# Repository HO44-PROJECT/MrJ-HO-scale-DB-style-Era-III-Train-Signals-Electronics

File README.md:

# Railway HO project Signals and electronics for my HO scale railway project

This is my own project for building model railway HO scale (1:87) Deutsche Bundesbahn (DB) style Era III (1945-1970) Train Signals following this specification.

This is part of a complete project involving:

- 3D printing: the signal bodies, 3 faces ([Maker World](https://makerworld.com/en/models/682526-mrj-ho-scale-db-signals-era-iii-3x-faces))
- Electronics (PCB design and soldering) ([github](https://github.com/HO44-PROJECT/MrJ-HO-scale-DB-style-Era-III-Train-Signals-Electronics))
- Arduino code (demo, DCC and JMRI integration) ([github](https://github.com/HO44-PROJECT/MrJ-HO-scale-DB-style-Era-III-Train-Signals-Arduino-Demo-Code))

## Another project to drive the signals

[MrJ-LayoutFX](https://github.com/HO44-PROJECT/MrJ-LayoutFX) grew out of these signals. It gives you a control
interface for an ESP32 that is driven by DCC commands and can generate lighting effects (signals, beacons, traffic
lights, campfires...) and drive other peripherals. You can flash it straight from your browser.
It is designed to work with a custom PCB with built-in DCC decoding,
[MrJ-LayoutFX-ESP32-PCB](https://github.com/HO44-PROJECT/MrJ-LayoutFX-ESP32-PCB) (ESP32 DevKitC), and also exists for
the Arduino Nano with [MrJ-LayoutFX-Nano-PCB](https://github.com/HO44-PROJECT/MrJ-LayoutFX-Nano-PCB).

This is what you will be able to build:

# What this repository provides

- the **gerber files** of the 2 PCB versions (production and breadboard), ready to send to a manufacturer
- the **wiring and test elements**: the level (VCC / GND) to apply on each wire for every signal aspect and every wiring test, and Fritzing parts to draw your circuit

**[Try the interactive 3D viewer](https://ho44-project.github.io/MrJ-HO-scale-DB-style-Era-III-Train-Signals-Electronics/documentation/prod/MrJ-DB-Era3-prod-viewer.html)**
(production PCB; the [breadboard version](https://ho44-project.github.io/MrJ-HO-scale-DB-style-Era-III-Train-Signals-Electronics/documentation/breadboard/MrJ-DB-Era3-breadboard-viewer.html) is there too).
Pick a signal, then an aspect: all LEDs off, all on, Hp0, Hp1...
The 3D view also helps you **place the LEDs**: turn the board around and see which LED goes where, and which ones
light for each aspect.

The breadboard version, for the three signals (block, entry, exit):

| Block signal | Entry signal | Exit signal |
|---|---|---|
|  |  |  |

## Production or breadboard?

Both boards have the same circuit and the same LEDs. They differ by how you connect them:

- **Production PCB**: the board that goes inside the signal. You solder your wires directly to the pads.
  This is the one to order for your layout.
- **Breadboard PCB**: the same board with pin headers, and room to solder the resistors on it.
  Plug it on a breadboard to test the wiring, the resistors and your controller (Arduino, DCC, JMRI) *before*
  building the real signals. It is a test tool, not meant to be installed on the layout.

If you only want to build the signals, order the production PCB. Order the breadboard one too if you want to test first.

## More pictures

The [images](images/) directory holds many pictures of the assembly (soldering with helpers, testing a signal,
disassembly), of the design (board, details, parts) and of the finished block, entry and exit signals.
The assembly pictures show the **procedure to follow**, in particular how to **use the jig**: a 3D printed part
that holds the LEDs and the PCB in place while you solder them.

# Resources

[wikipedia signals in Germany](https://en.wikipedia.org/wiki/Railway_signals_in_Germany)

These sites were a great source of inspiration:
* [stummi forum (DE)](https://www.stummiforum.de/t174376f21-Viessman-Signalbr-cke-mit-Arduino-gesteuert.html)
* [digital bahn (DE)] (https://www.digital-bahn.de/info_kompo/signale.htm)

# Project

This project contains Kicad project files and gerber to build PCBs using 1.8mm LEDs.

This PCB uses charlieplexing to reduce the number of wires. It is possible to build a block signal, input signal, or output signal with this PCB.
I designed my own wiring path to avoid using the POV effect to light multiple LEDs. Each situation for each signal is a simple combination of HIGH and LOW signals on all 4 pins.

It's possible to reduce the number of wires for the "Block Signal" (only 2 wires required) and the "Entry Signal" (only 3 wires required). See [documentation](documentation/).

I also need a special breadboard version to ease tests. This version allows soldering of resistors.

The **gerber.zip** files are enough to build the PCB from a manufacturer such as [jlcpcb](https://jlcpcb.com/). See the [release](release/) directory.

The PCB is designed to fit inside the 3D printed signals: see the
[3D model on Maker World](https://makerworld.com/en/models/682526-mrj-ho-scale-db-signals-era-iii-3x-faces).

# History

The version 2 is smaller than the version 1.
It solves the "shunting signal" Hp0 + Sh1 did not work because the right white LED did not light up.

This v3 is a better version as it fixes a distributed current problem.

# Repository content

| Directory | Content |
|---|---|
| [release](release/) | Gerber zips, ready to send to a PCB manufacturer (production and breadboard boards). |
| [source](source/) | KiCad 10 projects (schematic and PCB) of the two boards. |
| [library](library/) | KiCad footprints, 3D models and drawings of the 1.8 mm LEDs. |
| [documentation](documentation/) | Renders, interactive 3D viewers, and the wire levels (VCC / GND) for each signal aspect. |
| [images](images/) | Pictures of the assembly, the design and the finished signals. |
| [fritzing](fritzing/) | [Fritzing](https://fritzing.org) parts of the signals, to draw your circuit. |

The 3D printed signals themselves are on [Maker World](https://makerworld.com/en/models/682526-mrj-ho-scale-db-signals-era-iii-3x-faces).

The interactive viewers in [documentation](documentation/) must be served over http (for example from GitHub Pages).

# BOM:
* a PCB per signal. I ordered mine 0.8mm thickness from jlcpcb.com simply by uploading the gerber.zip file.
* 2 to 4 resistors 1/4 W from everywhere: 470 ohm for a 3.3 V supply, 1 kohm for a 5 V supply
* 1.8mm LEDs. I bought mine from aliexpress.com.

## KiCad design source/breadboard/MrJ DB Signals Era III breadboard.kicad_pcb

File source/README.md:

# source

KiCad 10 projects of the signal boards (schematic + PCB). Open the `.kicad_pro` file in KiCad.

| Folder | Board |
|---|---|
| `prod/` | Production PCB, wires are soldered to the pads. |
| `breadboard/` | Same circuit with pin headers, for prototyping on a breadboard. |

Each folder contains the project (`.kicad_pro`), the schematic (`.kicad_sch`) and the PCB (`.kicad_pcb`).
The LED footprints and 3D models come from [`../library`](../library).

These files are the single source of truth: everything in `documentation/`, `fritzing/` and
`release/` is derived from them.

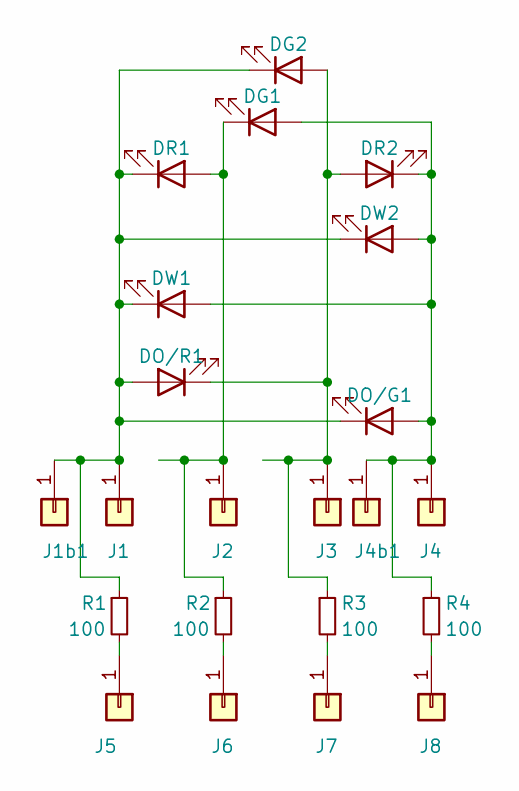
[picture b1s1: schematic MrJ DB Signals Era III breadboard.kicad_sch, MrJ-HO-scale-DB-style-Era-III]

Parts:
DG1, DG2: LED; LED_D1.8mm_W3.3mm_H2.4mm_mine
DO/G1: LED; LED_D1.8mm_W3.3mm_H2.4mm_mine
DO/R1: LED; LED_D1.8mm_W3.3mm_H2.4mm_mine
DR1, DR2: LED; LED_D1.8mm_W3.3mm_H2.4mm_mine
DW1, DW2: LED; LED_D1.8mm_W3.3mm_H2.4mm_mine
J1, J1b1, J2, J3, J4, J4b1: Conn_01x01; SolderWirePad_1x01_SMD_1x2mm
J5, J6, J7, J8: Conn_01x01; Pin_D0.9mm_L10.0mm_W2.4mm_FlatFork
R1, R2, R3, R4: 100; R_Axial_DIN0204_L3.6mm_D1.6mm_P7.62mm_Horizontal

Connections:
unnamed: DG1.2 (A), DO/G1.2 (A), DR2.1 (K), DW1.2 (A), DW2.2 (A), J4.1, J4b1.1, R4.1
unnamed: DG1.1 (K), DR1.2 (A), J2.1, R2.1
unnamed: DG2.2 (A), DO/R1.1 (K), DR2.2 (A), J3.1, R3.1
unnamed: DG2.1 (K), DO/G1.1 (K), DO/R1.2 (A), DR1.1 (K), DW1.1 (K), DW2.1 (K), J1.1, J1b1.1, R1.1
unnamed: J5.1, R1.2
unnamed: J6.1, R2.2
unnamed: J7.1, R3.2
unnamed: J8.1, R4.2

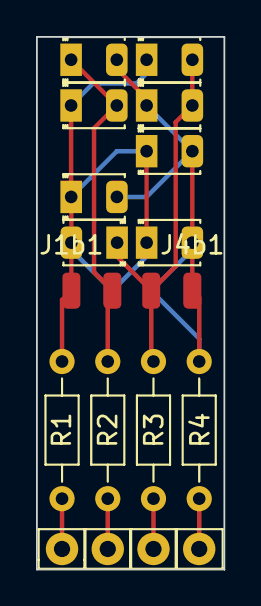
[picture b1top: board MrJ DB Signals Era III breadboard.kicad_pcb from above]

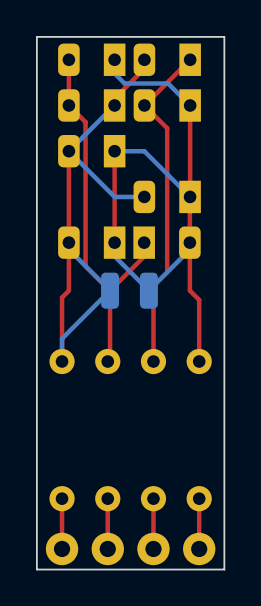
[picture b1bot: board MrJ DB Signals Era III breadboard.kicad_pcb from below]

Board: 2 copper layers, 10.4 x 29.6 mm, 22 parts (2 on the bottom side), 8 nets.

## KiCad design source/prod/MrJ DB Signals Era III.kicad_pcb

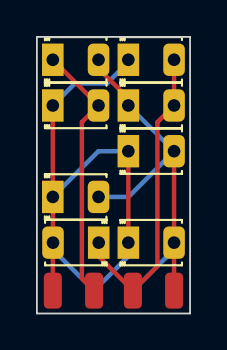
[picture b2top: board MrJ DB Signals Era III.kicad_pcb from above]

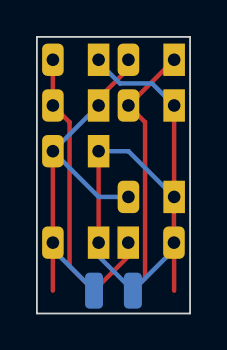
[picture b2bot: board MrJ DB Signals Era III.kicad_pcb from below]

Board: 2 copper layers, 8.5 x 15.4 mm, 14 parts (2 on the bottom side), 4 nets.

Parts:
DG1, DG2: LED; LED_D1.8mm_W3.3mm_H2.4mm_mine
DO/G1: LED; LED_D1.8mm_W3.3mm_H2.4mm_mine
DO/R2: LED; LED_D1.8mm_W3.3mm_H2.4mm_mine
DR1, DR2: LED; LED_D1.8mm_W3.3mm_H2.4mm_mine
DW1, DW2: LED; LED_D1.8mm_W3.3mm_H2.4mm_mine
J1, J1b1, J2, J3, J4, J4b1: Conn_01x01; SolderWirePad_1x01_SMD_1x2mm

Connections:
unnamed: DG1.2 (A), DO/G1.2 (A), DR2.1 (K), DW1.2 (A), DW2.2 (A), J4.1, J4b1.1
unnamed: DG1.1 (K), DR1.2 (A), J2.1
unnamed: DG2.2 (A), DO/R2.1 (K), DR2.2 (A), J3.1
unnamed: DG2.1 (K), DO/G1.1 (K), DO/R2.2 (A), DR1.1 (K), DW1.1 (K), DW2.1 (K), J1.1, J1b1.1

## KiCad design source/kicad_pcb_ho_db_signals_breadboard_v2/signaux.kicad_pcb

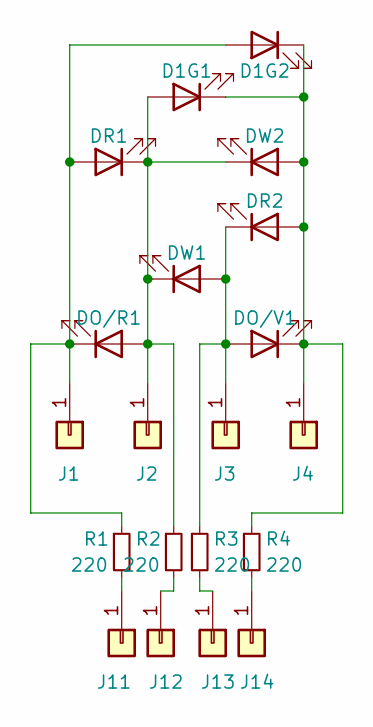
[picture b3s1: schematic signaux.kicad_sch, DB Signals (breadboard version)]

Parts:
D1G1, D1G2: LED; LED_D1.8mm_W3.3mm_H2.4mm_mine
DO/R1: LED; LED_D1.8mm_W3.3mm_H2.4mm_mine
DO/V1: LED; LED_D1.8mm_W3.3mm_H2.4mm_mine
DR1, DR2: LED; LED_D1.8mm_W3.3mm_H2.4mm_mine
DW1, DW2: LED; LED_D1.8mm_W3.3mm_H2.4mm_mine
J1, J2, J3, J4: Conn_01x01; SolderWirePad_1x01_SMD_1x2mm
J11, J12, J13, J14: Conn_01x01; Pin_D0.9mm_L10.0mm_W2.4mm_FlatFork
R1, R2, R3, R4: 220; R_Axial_DIN0204_L3.6mm_D1.6mm_P7.62mm_Horizontal

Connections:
unnamed: D1G1.2 (A), DO/R1.2 (A), DR1.1 (K), DW1.1 (K), DW2.1 (K), J2.1, R2.1
unnamed: D1G1.1 (K), D1G2.1 (K), DO/V1.1 (K), DR2.2 (A), DW2.2 (A), J4.1, R4.1
unnamed: D1G2.2 (A), DO/R1.1 (K), DR1.2 (A), J1.1, R1.1
unnamed: DO/V1.2 (A), DR2.1 (K), DW1.2 (A), J3.1, R3.1
unnamed: J11.1, R1.2
unnamed: J12.1, R2.2
unnamed: J13.1, R3.2
unnamed: J14.1, R4.2

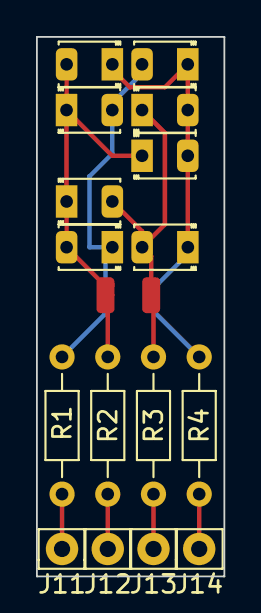
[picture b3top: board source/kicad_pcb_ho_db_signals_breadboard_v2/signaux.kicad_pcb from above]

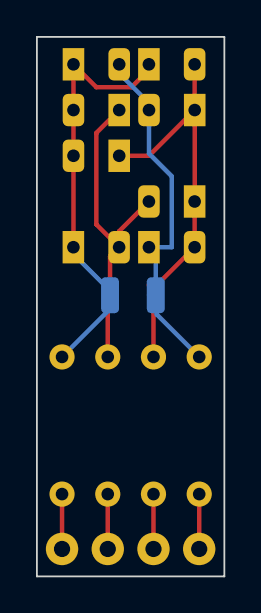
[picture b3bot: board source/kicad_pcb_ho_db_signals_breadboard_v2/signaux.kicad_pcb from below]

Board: 2 copper layers, 10.4 x 30.0 mm, 20 parts (2 on the bottom side), 8 nets.

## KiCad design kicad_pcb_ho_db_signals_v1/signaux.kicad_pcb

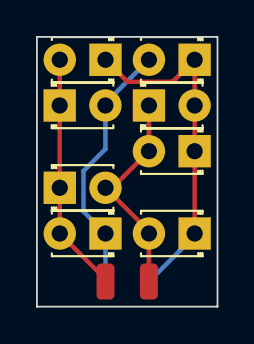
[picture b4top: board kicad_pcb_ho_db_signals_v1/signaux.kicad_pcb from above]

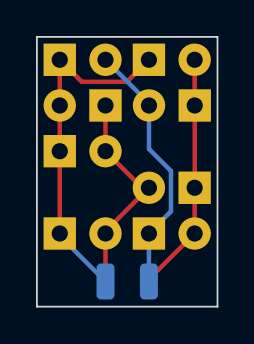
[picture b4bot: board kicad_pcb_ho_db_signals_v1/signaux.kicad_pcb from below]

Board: 2 copper layers, 10.0 x 15.0 mm, 12 parts (2 on the bottom side), 4 nets.

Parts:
D1G1, D1G2, D2R1, D3R1, D4W1, D5W1, D6O1, D7O2: LED; LED_D1.8mm_W3.3mm_H2.4mm
J1, J2, J3, J4: Conn_01x01; SolderWirePad_1x01_SMD_1x2mm

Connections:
unnamed: D1G1.2 (A), D2R1.1 (K), D5W1.1 (K), D6O1.2 (A), J2.1
unnamed: D1G1.1 (K), D1G2.1 (K), D3R1.2 (A), D4W1.1 (K), D7O2.1 (K), J4.1
unnamed: D1G2.2 (A), D2R1.2 (A), D6O1.1 (K), J1.1
unnamed: D3R1.1 (K), D4W1.2 (A), D5W1.2 (A), D7O2.2 (A), J3.1

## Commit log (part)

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2024-02-17 first shot
2024-10-03 addon
2024-10-03 gerber files
2024-10-05 reorganisation
2024-10-05 work
2024-10-08 Create LICENSE
2024-10-19 Documentation
2024-10-19 reorg
